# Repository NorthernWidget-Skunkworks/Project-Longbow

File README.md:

# Project-Longbow
Eagle files for a RS-485 range extender system, designed to go between I2C and RS-485 (or simply convert RS-485 to UART. Designed to work in unison with TP-Downhole Longbow system from Northern Widget

<br>
<br />This work is licensed under a <a rel="license" href="http://creativecommons.org/licenses/by-sa/4.0/">Creative Commons Attribution-ShareAlike 4.0 International License</a>.

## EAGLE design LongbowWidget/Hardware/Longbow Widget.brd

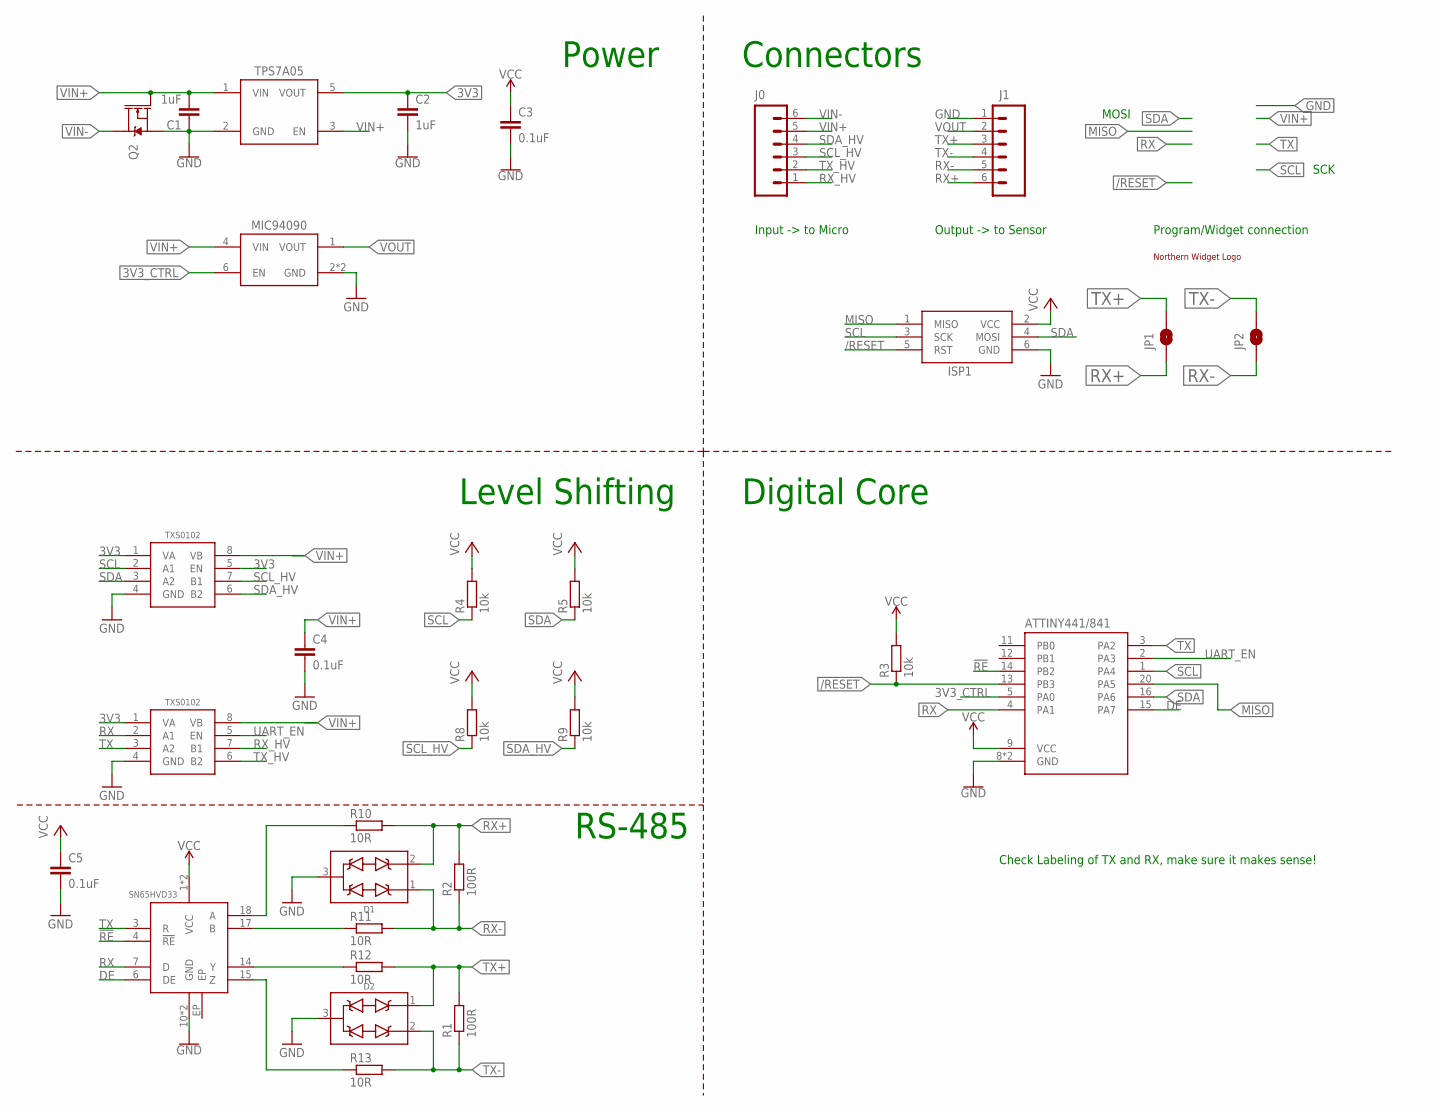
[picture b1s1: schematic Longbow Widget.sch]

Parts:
C1, C2: 1uF; C0603
C3, C4, C5: 0.1uF; C0402
D1, D2: TVSSM712; SOT23-3
ISP1: AVRISP1.27MM; 2X3_1.27
J0, J1: CONN_6SCREW_2.54; 1X06_SCREW
JP1, JP2: JUMPER-SMT_2_NO_SILK; SMT-JUMPER_2_NO_SILK
Q2: DMG3404; SOT23-3
R1, R2: 100R; R0402
R3, R4, R5, R8, R9: 10k; R0402
R10, R11, R12, R13: 10R; R0603; MPN CRCW060310R0FKEAHP; DIGIKEY 541-10.0SCT-ND
U1: TPS7A0533DBV; SOT23-5; DIGIKEY 296-TPS7A0533PDBVRCT-ND
U2: SN65HVD33RHL; VQFN-20_POWER
U$1: MIC94090C6; SC-70_6
U$2: ATTINY441/841VQFN; VQFN-20
U$3, U$6: TXS0102DQM; DQM_R-PX2SON-N8
U$4: NWLOGO_MED

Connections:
3V3: C2.1, C3.1, C5.1, ISP1.2 (VCC), R3.2, R4.2, R5.2, U1.5 (VOUT), U2.1 (VCC), U2.20 (VCC), U$2.9 (VCC), U$3.1 (VA), U$3.5 (EN), U$6.1 (VA)
3V3_CTRL: U$1.6 (EN), U$2.5 (PA0)
!RE: U2.4 (!RE), U$2.14 (PB2)
/RESET: ISP1.5 (RST), R3.1, U$2.13 (PB3)
DE: U2.6 (DE), U$2.15 (PA7)
GND: C1.1, C2.2, C3.2, C4.2, C5.2, D1.3 (COM), D2.3 (COM), ISP1.6 (GND), J1.1, Q2.2 (S), U1.2 (GND), U2.10 (GND), U2.11 (GND), U$1.2 (GND), U$1.5 (GND), U$2.8 (GND), U$2.EP (GND), U$3.4 (GND), U$6.4 (GND)
MISO: ISP1.1 (MISO), U$2.20 (PA5)
unnamed: R10.1, U2.18 (A)
unnamed: R11.1, U2.17 (B)
unnamed: R12.1, U2.14 (Y)
unnamed: R13.1, U2.15 (Z)
RX: U2.7 (D), U$2.4 (PA1), U$6.2 (A1)
RX+: D1.2 (D2), J1.6, JP1.1, R2.2, R10.2
RX-: D1.1 (D1), J1.5, JP2.1, R2.1, R11.2
RX_HV: J0.1, U$6.7 (B1)
SCL: ISP1.3 (SCK), R4.1, U$2.1 (PA4), U$3.2 (A1)
SCL_HV: J0.3, R8.1, U$3.7 (B1)
SDA: ISP1.4 (MOSI), R5.1, U$2.16 (PA6), U$3.3 (A2)
SDA_HV: J0.4, R9.1, U$3.6 (B2)
TX: U2.3 (R), U$2.3 (PA2), U$6.3 (A2)
TX+: D2.1 (D1), J1.3, JP1.2, R1.2, R12.2
TX-: D2.2 (D2), J1.4, JP2.2, R1.1, R13.2
TX_HV: J0.2, U$6.6 (B2)
UART_EN: U$2.2 (PA3), U$6.5 (EN)
VIN+: C1.2, C4.1, J0.5, Q2.1 (G), R8.2, R9.2, U1.1 (VIN), U1.3 (EN), U$1.4 (VIN), U$3.8 (VB), U$6.8 (VB)
VIN-: J0.6, Q2.3 (D)
VOUT: J1.2, U$1.1 (VOUT)

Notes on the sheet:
Check Labeling of TX and RX, make sure it makes sense!
MOSI
SCK
Power
Connectors
Level Shifting
Digital Core
RS-485
Input -> to Micro
Output -> to Sensor
Program/Widget connection

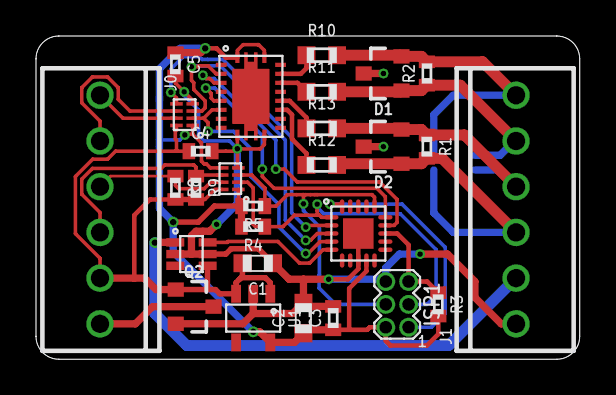
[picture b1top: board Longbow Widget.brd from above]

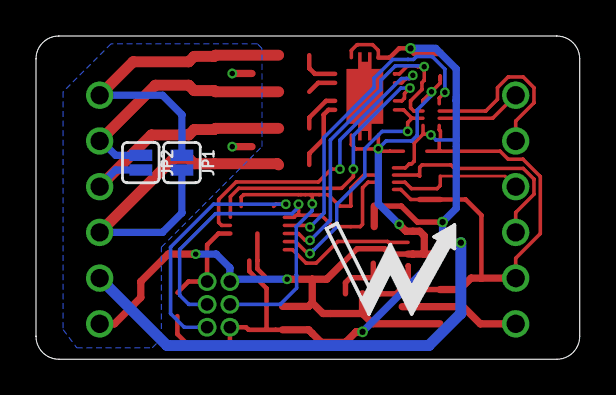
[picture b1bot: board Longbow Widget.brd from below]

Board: 2 copper layers, 30.2 x 18.0 mm, 31 parts (3 on the bottom side), 27 nets.

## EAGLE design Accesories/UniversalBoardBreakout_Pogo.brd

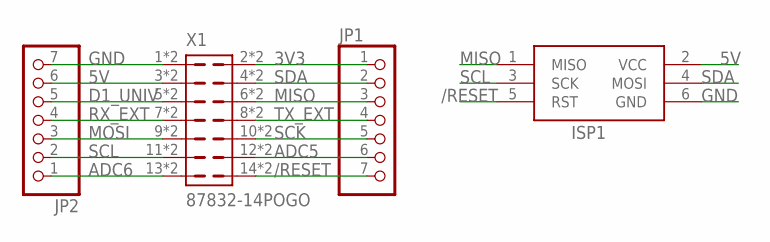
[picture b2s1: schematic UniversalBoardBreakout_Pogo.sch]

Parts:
ISP1: AVRISP-6; AVRISP
JP1, JP2: CONN_7; 1X07
X1: 87832-14POGO; 87832-14_POGO

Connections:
3V3: JP1.1, X1.2, X1.P2 (2)
5V: ISP1.2 (VCC), JP2.6, X1.3, X1.P3 (3)
/RESET: ISP1.5 (RST), JP1.7, X1.14, X1.P14 (14)
ADC5: JP1.6, X1.12, X1.P12 (12)
ADC6: JP2.1, X1.13, X1.P13 (13)
D1_UNIV: JP2.5, X1.5, X1.P5 (5)
GND: ISP1.6 (GND), JP2.7, X1.1, X1.P1 (1)
MISO: ISP1.1 (MISO), JP1.3, X1.6, X1.P6 (6)
MOSI: JP2.3, X1.9, X1.P9 (9)
RX_EXT: JP2.4, X1.7, X1.P7 (7)
SCK: JP1.5, X1.10, X1.P10 (10)
SCL: ISP1.3 (SCK), JP2.2, X1.11, X1.P11 (11)
SDA: ISP1.4 (MOSI), JP1.2, X1.4, X1.P4 (4)
TX_EXT: JP1.4, X1.8, X1.P8 (8)

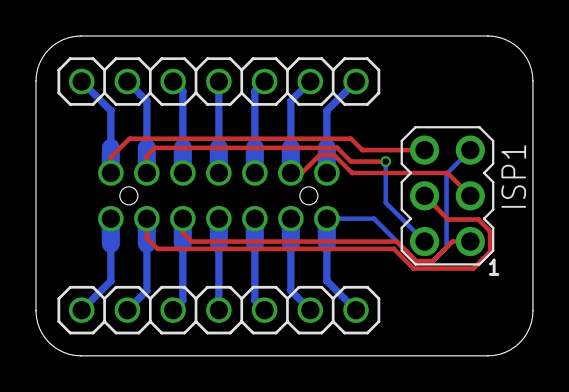
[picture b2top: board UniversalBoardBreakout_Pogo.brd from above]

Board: 2 copper layers, 27.6 x 17.8 mm, 4 parts (1 on the bottom side), 14 nets.

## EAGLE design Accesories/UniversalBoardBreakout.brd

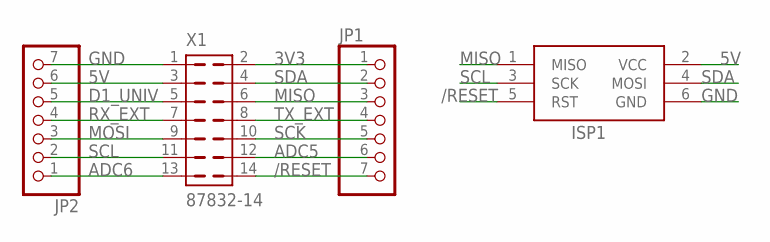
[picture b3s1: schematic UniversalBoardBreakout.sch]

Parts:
ISP1: AVRISP-6; AVRISP
JP1, JP2: CONN_7; 1X07
X1: 87832-14

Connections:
3V3: JP1.1, X1.2
5V: ISP1.2 (VCC), JP2.6, X1.3
/RESET: ISP1.5 (RST), JP1.7, X1.14
ADC5: JP1.6, X1.12
ADC6: JP2.1, X1.13
D1_UNIV: JP2.5, X1.5
GND: ISP1.6 (GND), JP2.7, X1.1
MISO: ISP1.1 (MISO), JP1.3, X1.6
MOSI: JP2.3, X1.9
RX_EXT: JP2.4, X1.7
SCK: JP1.5, X1.10
SCL: ISP1.3 (SCK), JP2.2, X1.11
SDA: ISP1.4 (MOSI), JP1.2, X1.4
TX_EXT: JP1.4, X1.8

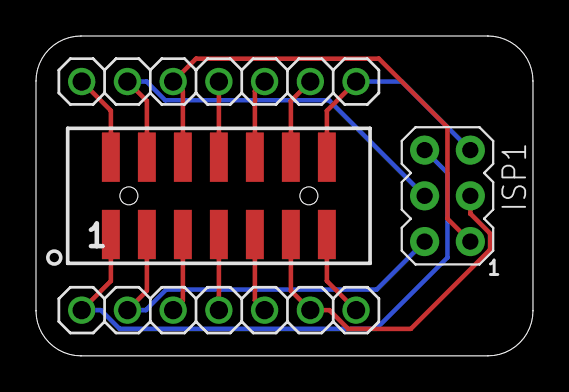
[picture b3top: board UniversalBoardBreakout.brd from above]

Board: 2 copper layers, 27.6 x 17.8 mm, 4 parts (0 on the bottom side), 14 nets.

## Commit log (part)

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2018-03-01 Initial comit of Longbow widget, Univerisal header breakout
2018-08-24 Added firmware for longbow widget
    Rough but functional code ready for ALPHA testing and revision. Size reduction likely needed along with some feature addition to match with the more developed TP-Downhole longbow firmware
2018-08-28 Remade Longbow Widget Firmware, BETA version
    Remade the firmware from a low level, changed the structure to support the updated Longbow protocol and supports read and write for packets
    Need to add:
    Figure out weird delay issue
    Add internal CRC check
    Add additional control abilities (more than just write value)
2018-08-28 Added notes for improvments
    Added comment notes for improvements:
    Read values from EEPROM for baud and address
    Set address (I2C) via response to general address call
    Make baud rate user settable using the control register
2018-08-29 Improved Longbow Widget Firmware, added interface software
    Added user settable features to the longbow widget firmware, added CRC check, etc. Firmware is in BETA stage, nearly ready for wide scale testing.
    Created a software interface demo for communicating with the longbow widget from an Arduino
    Both files need cleanup, some commenting and aesthetic changes, functionally 90% there
2018-08-29 Cleanup and documentation
2018-08-30 Updated Longbow Widget schematic, very preliminary board layout
    Added fixes for many of the issues to the schematic, made very preliminary board layout
    Likely to add some kind of transient protection to Longbow Widget, have left space on preliminary board layout to add in later
2018-08-31 Preliminary layout for Longbow Widget complete
    Needs cleanup and changes to silk screen before review, should be nearly functional (should add polygon pours for power on input side). Also added preliminary BOM, which requires update with new part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
2018-09-05 Cleaned up Widget
    Cleaned up layout of widget, adjusted silkscreen, fixed pinout issue, generated final gerbers, ready for prototype
2018-09-06 Final designs for Longbow Widget v0.1 and Universal Breakout Pogo board
    Added final design (minor silk screen additions) of the Longbow widget, also designed a modified Universal breakout which has support for pogo pins. Generated final gerbers for both as well
2018-09-07 Fixed part numbers on Longbow Widget, generated new BOMs
    Parts list is updated and fully auto generating
2018-09-07 Fixed part number for RS-485 driver
    Fixed the part number in the BOM for the RS-485 driver
2018-09-10 Updated Longbow Widget to use new Frames
    Updated to used new frames without Creative Commons text (caused issues)
2018-09-27 Added reset and set address ability
    Added reset ability to longbow widget firmware, still needs verification with reworked hardware. Currently data lines do not shut off so only browns out TP-Downhole, does not force reset. Hardware im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
2018-09-29 Updated gerbers for solder stencils
    Updated folder of gerbers for longbow widget (newest gerbers were only in Zip file, so never overwrote old ones), then generated SVG (-> DXF) of paste layer to use for laser cutting solder stencil
2018-10-10 Updated Longbow Interface
    Added address search functionality to the demo
2018-10-17 Firmware hotfix, v0.0
    Hotfix for the firmware for Longbow widget. EEPROM was randomly being overwritten/altered, removed all write to EEPROM commands to provide stability. Removed ability to set address/baud rate on the f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
2018-10-19 Updated Longbow Widget, v0.2 ready for review
    Made changes to new level shifters, RS485 driver with output shutoff, replaced mosfet with load switch, converted MCU to QFN package. Ready for final review
2018-10-27 Longbow Widget v0.2 sent to fab
    Minor edits to silkscreen on longbow widget, v0.2 timeline, generated gerbers for Longbow Widget
2018-11-01 Added folder system and design PDFs
    Added schematic and board PDFs for v0.2
2018-11-07 Added v0.1.0 firmware
    Added firmware with support for v0.2 hardware
2018-12-14 Added firmware v0.1.1, packet description doc
    Added updated firmware version, v0.1.1, fixes intermittent transmission failure on v0.2 hardware
2018-12-18 CC-BY-SA
2019-07-08 Minor firmware updates
2019-07-08 Added half duplex firmware variant
2020-02-20 Updated to v0.3
    Minor update, added jumpers to allow for conversion to 2 wire RS485 without external jumping/connection. Made edits in Eagle, generated new gerber files and updated BoM to reflect "jumper" parts
2020-02-20 Added quote zip file
2020-04-28 Added A and B value note in schematic
2020-04-30 stencil mount
2020-04-30 Deprecated design files
2020-04-30 From deprecated TLog header
2020-04-30 Deprecated connector for TLog
2020-04-30 No more accessories; no need for nested folders
2020-04-30 rm filename spaces
2020-04-30 vim swap
2020-04-30 rm deprecated; rm spaces
2020-04-30 Deprecated firmware
2020-04-30 rm version numbers from filenames
2020-04-30 Goodbye original! Live on history!
2020-04-30 Label A+ and B- for half duplex
2020-04-30 GPL for code

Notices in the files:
parts and their libraries:
bschulz: This work is licensed under the Creative Commons Attribution-ShareAlike 4.0
SparkFun-PowerSymbols: Licensing: Creative Commons ShareAlike 4.0 International - https://creativecommons.org/licenses/by-sa/4.0
